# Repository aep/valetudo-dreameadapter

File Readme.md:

# Dreame Breakout

This is a cheaper version of the original [valetudo-dreameadapter](https://github.com/Hypfer/valetudo-dreameadapter)
for rooting dreame robots.

It is optimized for manufacturing and can be completely assembled by JLC using the files in "production".
For that reason, it is less useful for developers and really only the minimum needed for user to root a bot.

I'll update this readme once someone tested it to actually work.

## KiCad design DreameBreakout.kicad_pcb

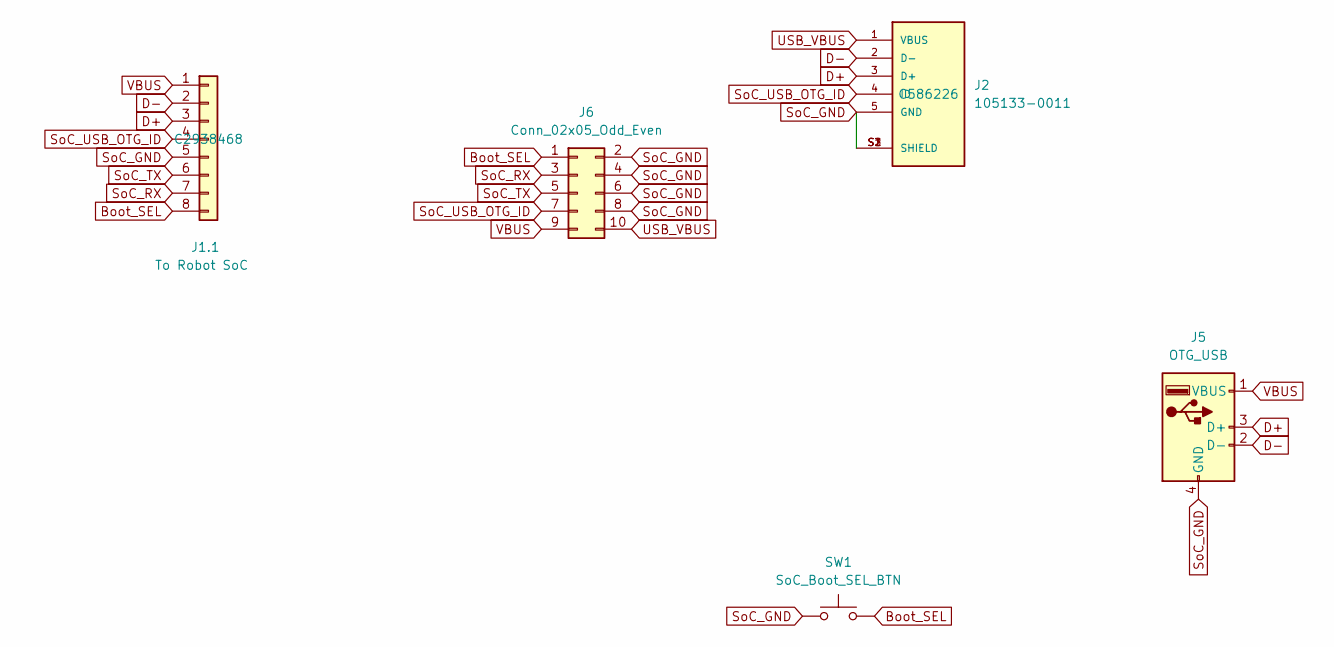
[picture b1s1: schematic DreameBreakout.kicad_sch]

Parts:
J1.1: To Robot SoC; PinHeader_1x08_P2.00mm_Horizontal; JLC# C2938468
J2: 105133-0011; MOLEX_105133-0011; PARTREV C; JLC# C586226
J5: OTG_USB; ONSHORE_USB-A1VSB6; JLC# C708904
J6: Conn_02x05_Odd_Even; PinHeader_2x05_P2.54mm_Vertical; JLC# C6332208
SW1: SoC_Boot_SEL_BTN; SW_TH_Tactile_Omron_B3F-10xx; JLC# C93153

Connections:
Boot_SEL: J1.1.8, J6.1, SW1.2
D+: J1.1.3, J2.3 (D+), J5.3 (D+)
D-: J1.1.2, J2.2 (D-), J5.2 (D-)
SoC_GND: J1.1.5, J2.5 (GND), J2.S1 (SHIELD), J2.S2 (SHIELD), J2.S3 (SHIELD), J5.4 (GND), J6.2, J6.4, J6.6, J6.8, SW1.1
SoC_RX: J1.1.7, J6.3
SoC_TX: J1.1.6, J6.5
SoC_USB_OTG_ID: J1.1.4, J2.4 (ID), J6.7
USB_VBUS: J2.1 (VBUS), J6.10
VBUS: J1.1.1, J5.1 (VBUS), J6.9

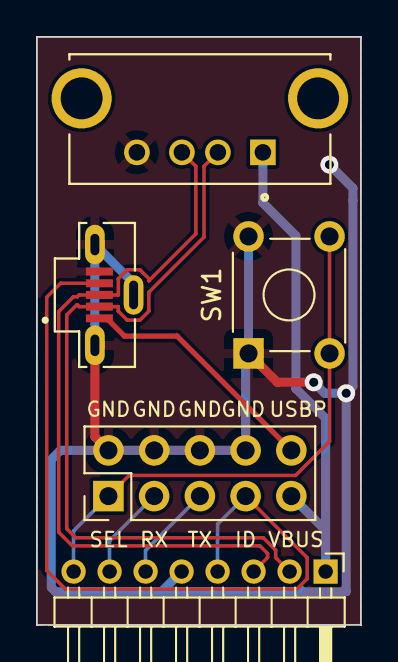
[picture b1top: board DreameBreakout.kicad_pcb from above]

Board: 2 copper layers, 18.0 x 32.7 mm, 5 parts (0 on the bottom side), 9 nets.

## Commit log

2023-09-15 init
